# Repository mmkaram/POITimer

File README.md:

# Distance to POI Display

## Overview
A small ESP32 project that shows the **current travel time** and **estimated arrival time (ETA)** to a predefined point of interest (POI) on a 16×2 LCD. Useful as a desk or wall display for quick, at‑a‑glance commute info.

## How it works
The ESP32 connects to WiFi, queries the TomTom Routing API for live traffic data, and calculates both the travel duration and ETA using NTP time synchronization. The results are refreshed periodically and displayed on the LCD.

## Setup
1. Copy `secrets.example.h` to `secrets.h`
2. Fill in your actual credentials in `secrets.h`
3. Upload to your ESP32

## TODO:
- [X] Have important variables in non uploaded config files
- [X] Print time to destination to LCD
- [X] Print estimated arrival time to LCD

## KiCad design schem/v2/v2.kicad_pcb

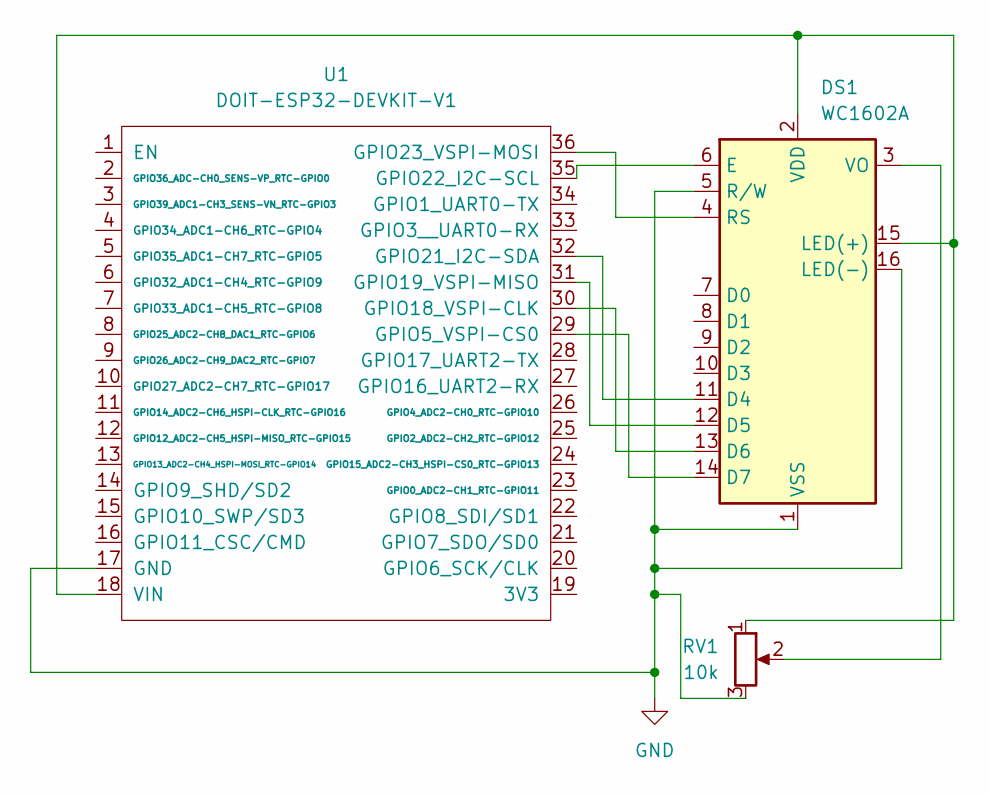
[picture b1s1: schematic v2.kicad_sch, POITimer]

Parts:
DS1: WC1602A
RV1: 10k; Potentiometer_Bourns_3296W_Vertical
U1: DOIT-ESP32-DEVKIT-V1; ESP32-DOIT-DEVKIT

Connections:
GND: DS1.1 (VSS), DS1.5 (R/W), DS1.16 (LED(-)), RV1.3, U1.17 (GND)
unnamed: DS1.11 (D4), U1.32 (GPIO21_I2C-SDA)
unnamed: DS1.12 (D5), U1.31 (GPIO19_VSPI-MISO)
unnamed: DS1.13 (D6), U1.30 (GPIO18_VSPI-CLK)
unnamed: DS1.14 (D7), U1.29 (GPIO5_VSPI-CS0)
unnamed: DS1.6 (E), U1.35 (GPIO22_I2C-SCL)
unnamed: DS1.2 (VDD), DS1.15 (LED(+)), RV1.1, U1.18 (VIN)
unnamed: DS1.4 (RS), U1.36 (GPIO23_VSPI-MOSI)
unnamed: DS1.3 (VO), RV1.2

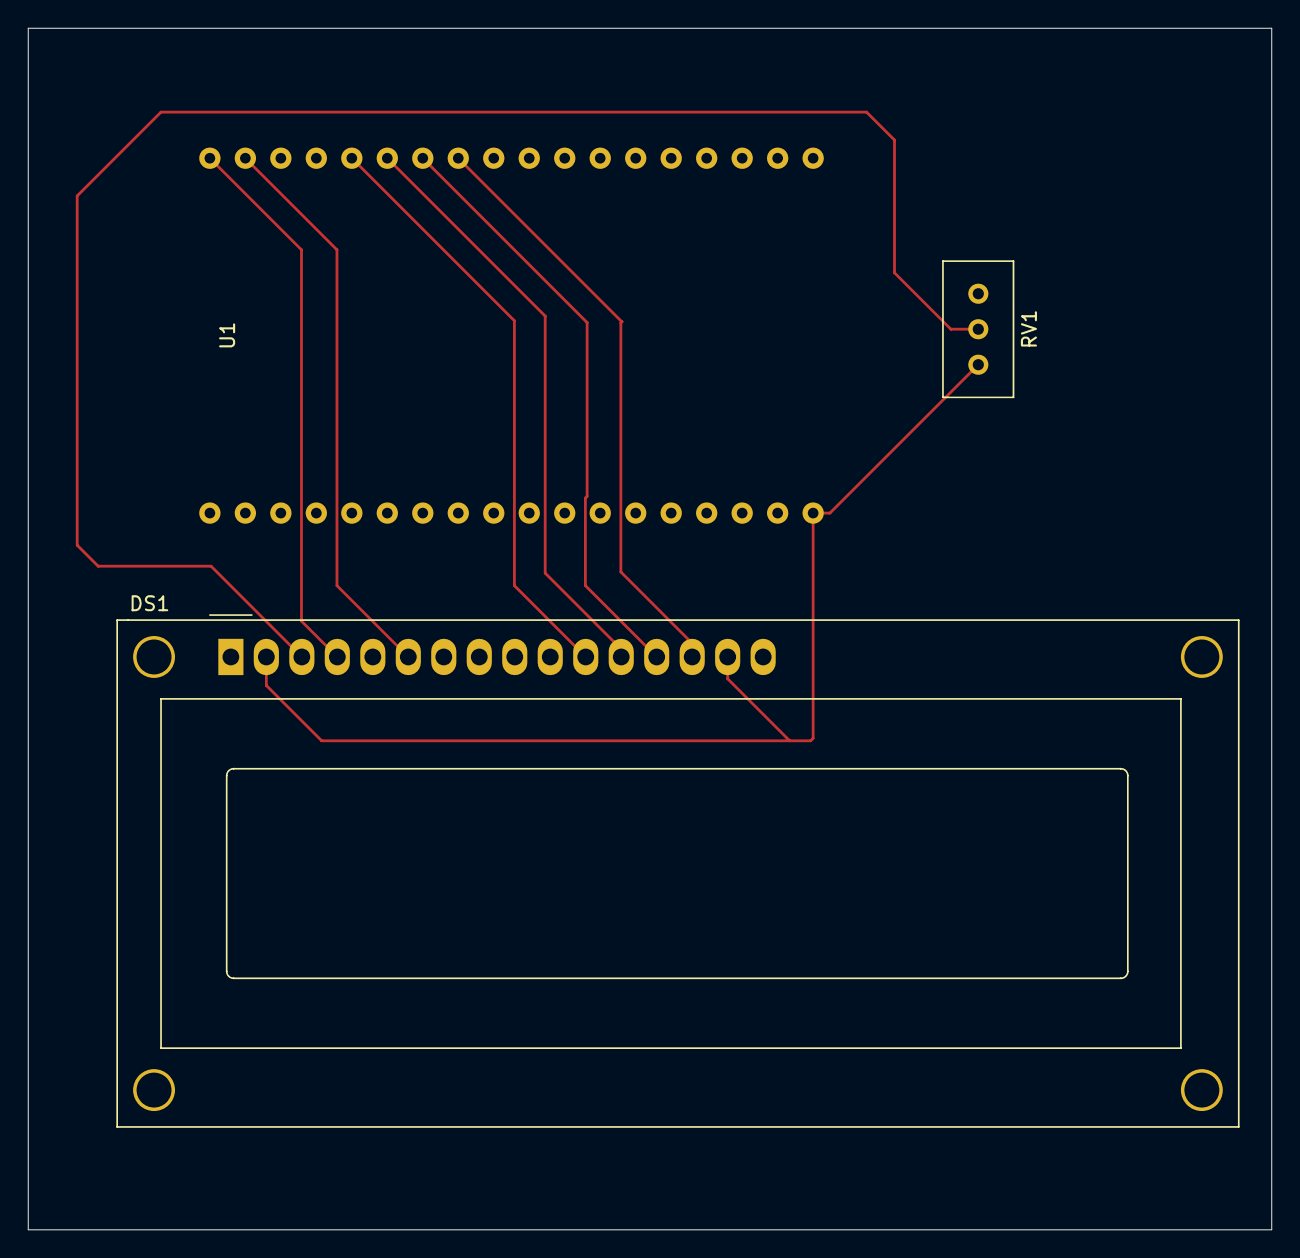
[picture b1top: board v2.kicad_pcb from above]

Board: 2 copper layers, 89.0 x 86.0 mm, 3 parts (0 on the bottom side), 9 nets.

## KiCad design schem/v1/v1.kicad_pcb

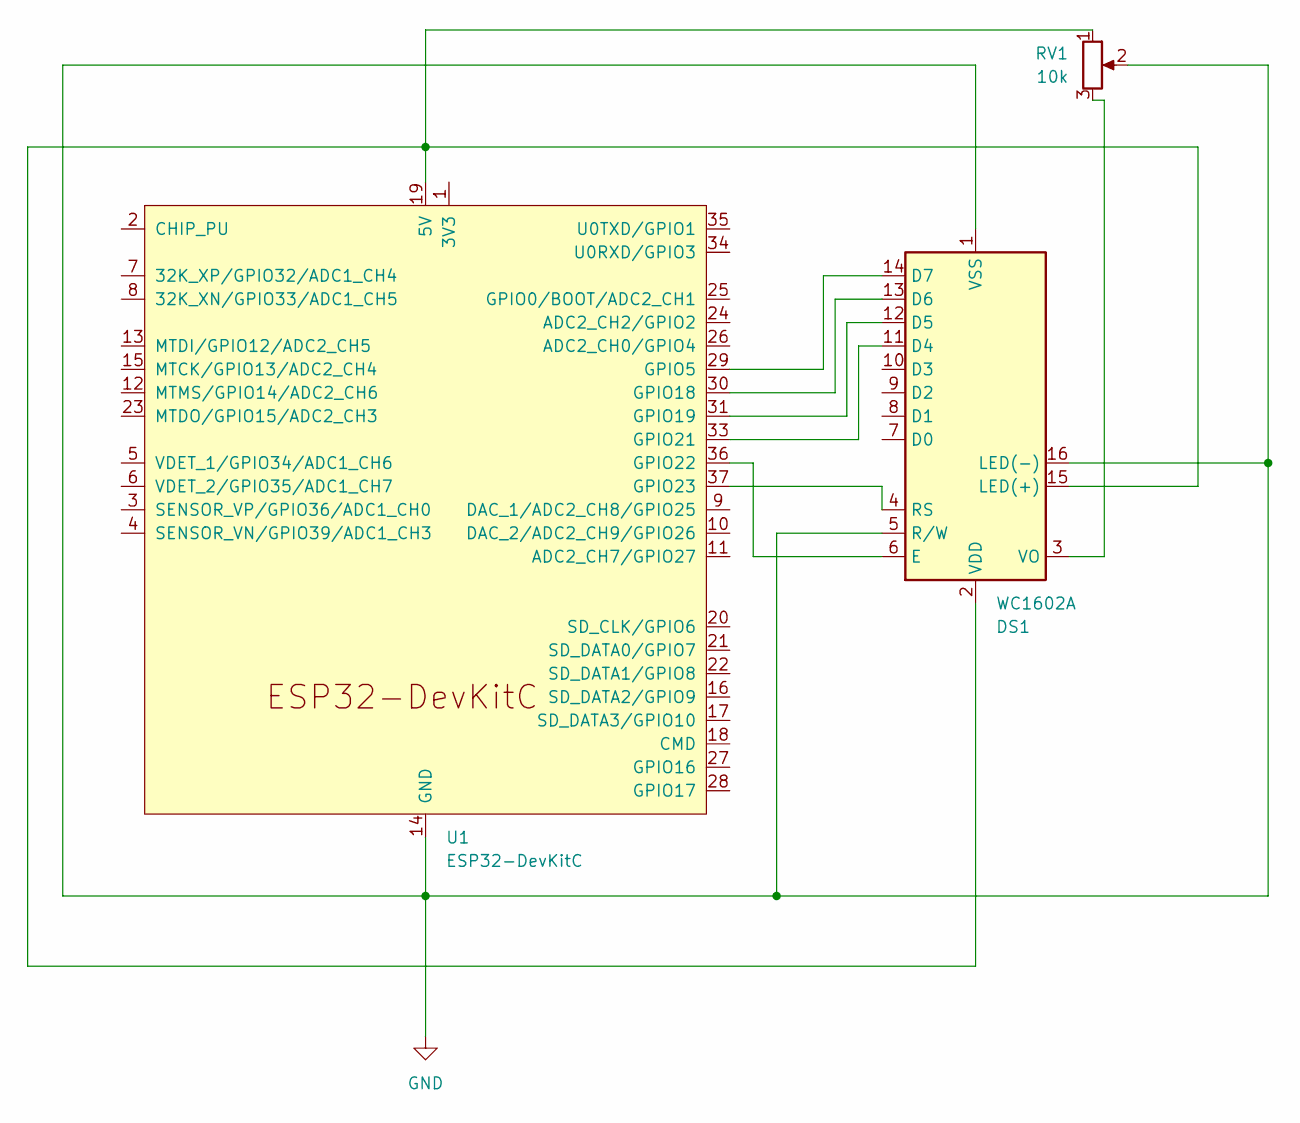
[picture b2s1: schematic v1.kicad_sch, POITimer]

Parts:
DS1: WC1602A
RV1: 10k; Potentiometer_ACP_CA6-VSMD_Vertical
U1: ESP32-DevKitC

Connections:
GND: DS1.1 (VSS), DS1.5 (R/W), DS1.16 (LED(-)), RV1.2, U1.14 (GND), U1.32 (GND), U1.38 (GND)
unnamed: DS1.11 (D4), U1.33 (GPIO21)
unnamed: DS1.12 (D5), U1.31 (GPIO19)
unnamed: DS1.13 (D6), U1.30 (GPIO18)
unnamed: DS1.14 (D7), U1.29 (GPIO5)
unnamed: DS1.6 (E), U1.36 (GPIO22)
unnamed: DS1.2 (VDD), DS1.15 (LED(+)), RV1.1, U1.19 (5V)
unnamed: DS1.4 (RS), U1.37 (GPIO23)
unnamed: DS1.3 (VO), RV1.3

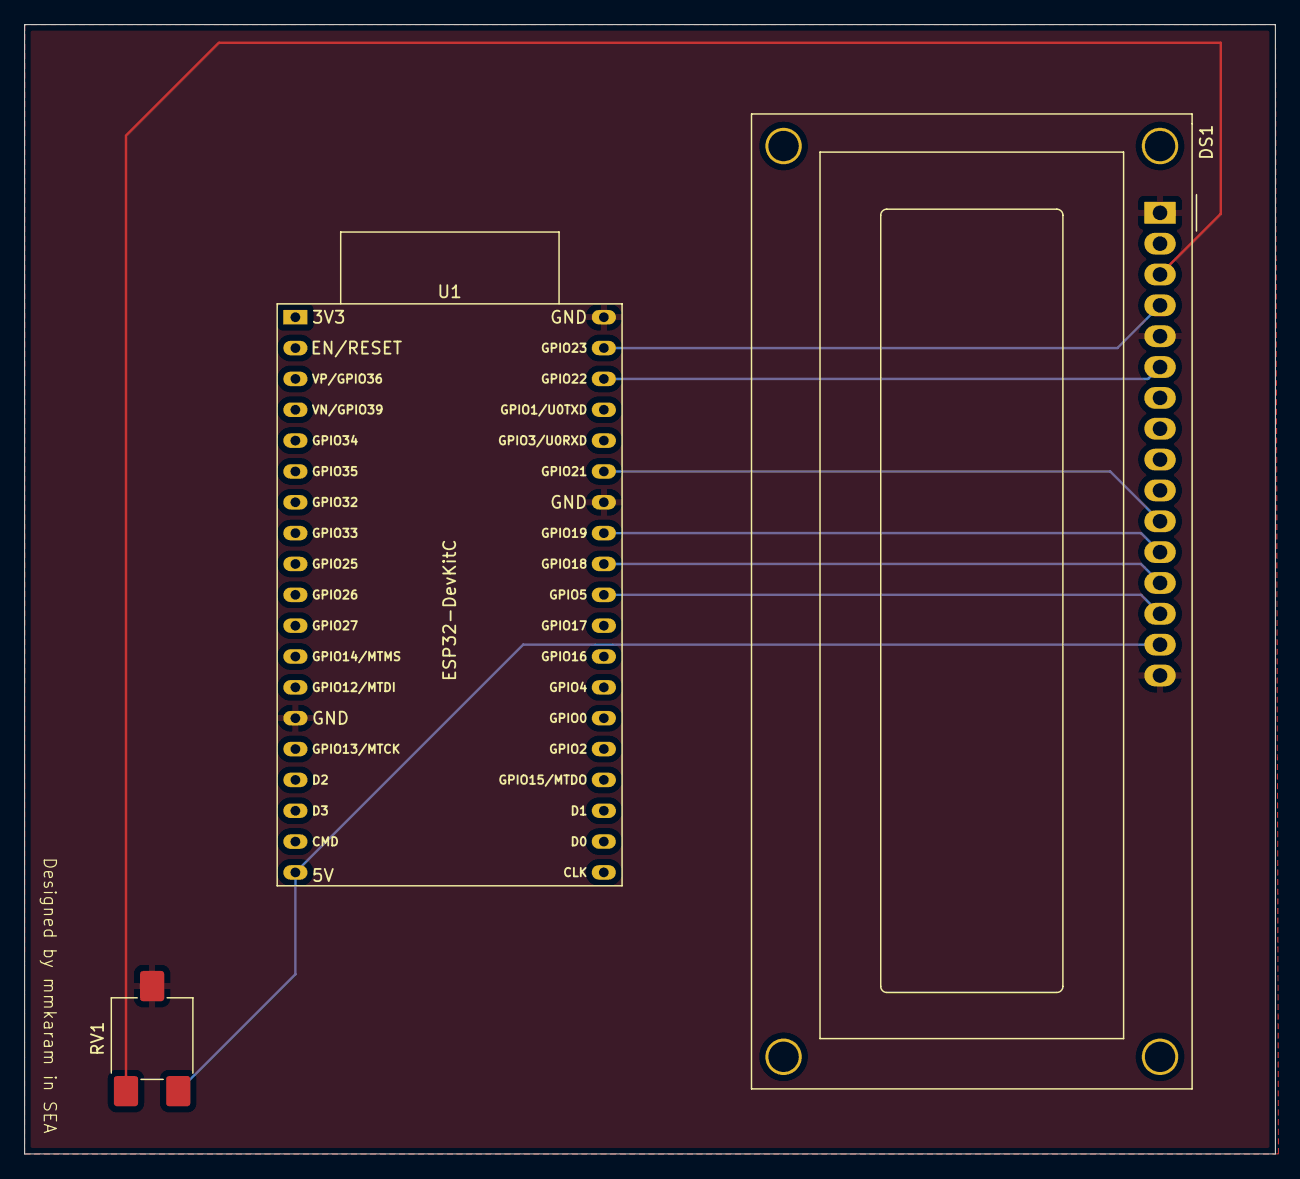
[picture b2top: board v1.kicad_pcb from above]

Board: 2 copper layers, 103.0 x 93.0 mm, 3 parts (0 on the bottom side), 9 nets.

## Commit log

2025-12-23 init
2025-12-24 add v1 schem
2025-12-25 start of v2 and doit esp32 devkit lib
2025-12-25 v2 schem+pcb connected
2025-12-27 added v3 double sided WIP
